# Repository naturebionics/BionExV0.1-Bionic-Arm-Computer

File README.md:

# BionExV0.1-Bionic-Arm-Computer
BionEx Bionic Limbs Computer

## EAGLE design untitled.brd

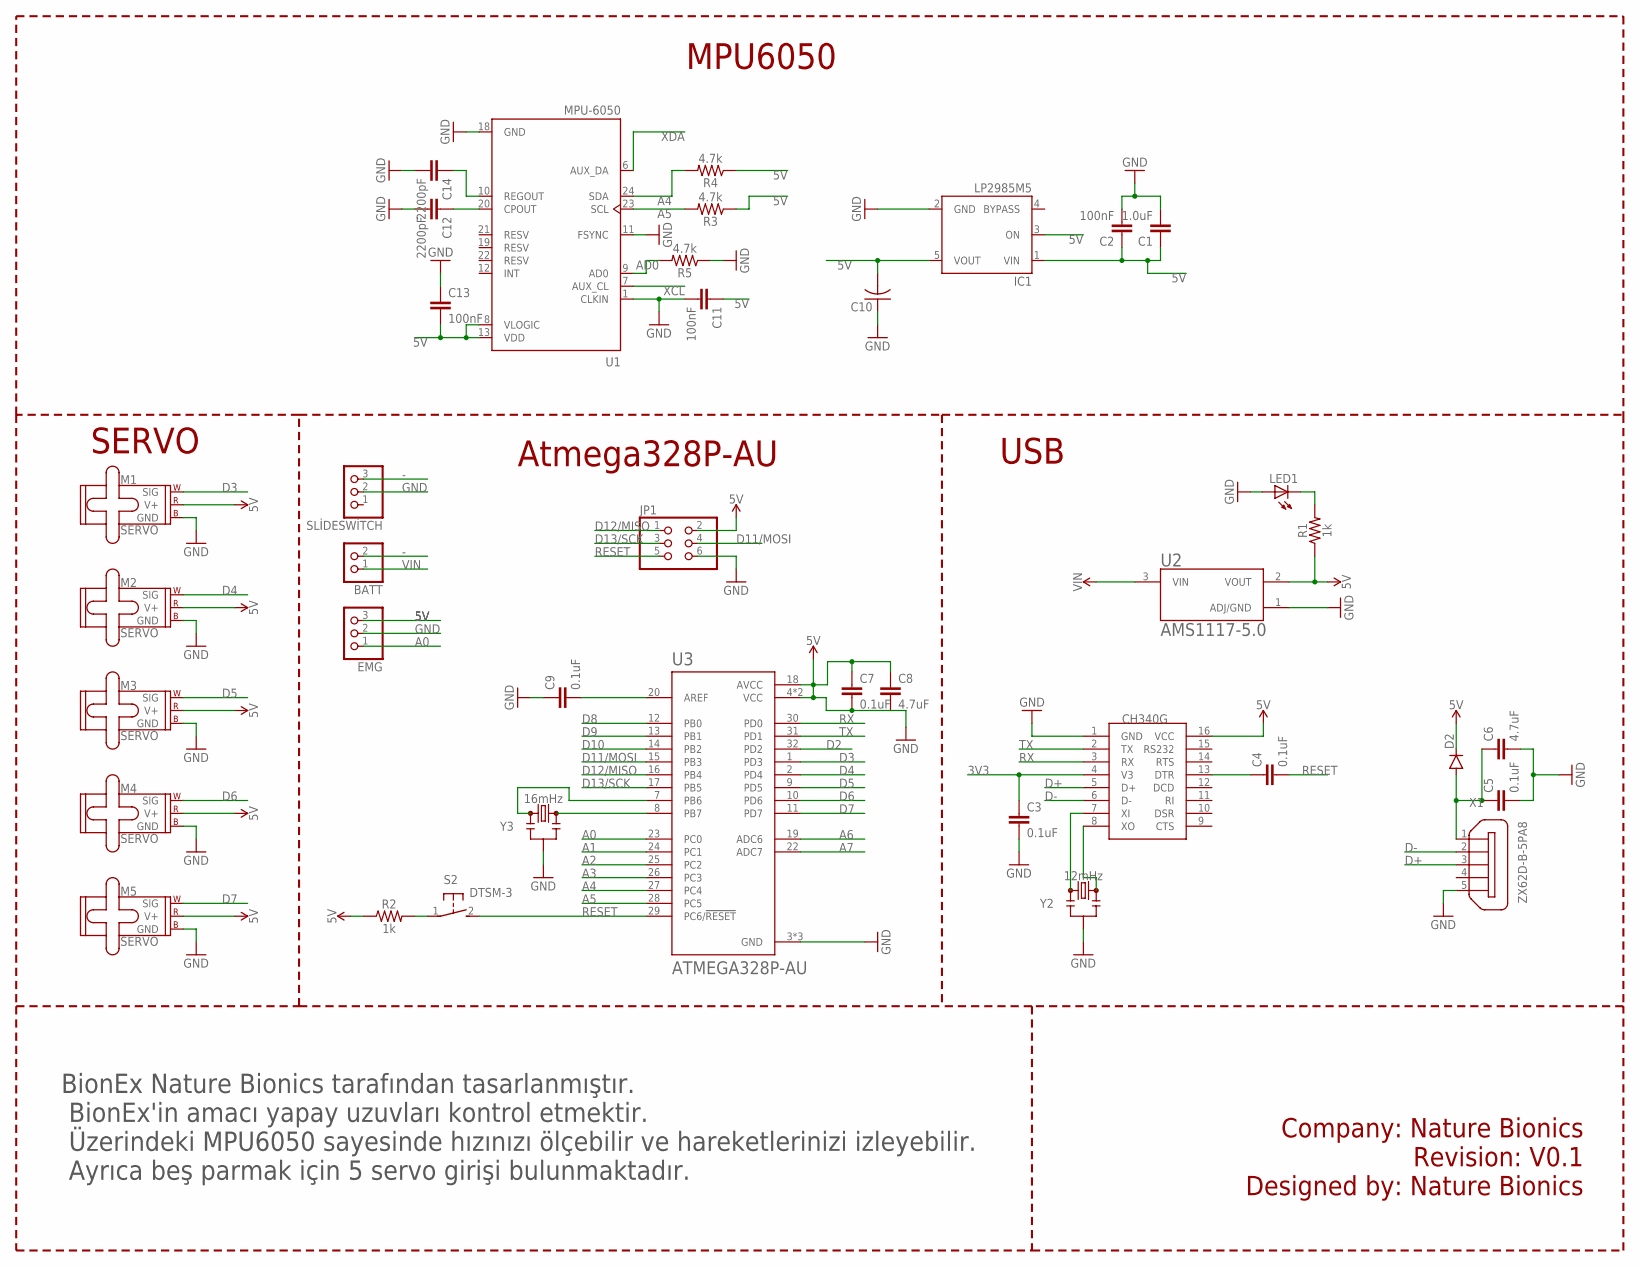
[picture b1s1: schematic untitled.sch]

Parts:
BATT: PINHD-1X2; 1X02
C1: 1.0uF; 0603
C2, C11, C13: 100nF; 0603
C3, C4, C5, C7, C9: 0.1uF; 0805
C6, C8: 4.7uF; 0603
C10: C-US_TANTALUM-1206(3216-METRIC); CAPM3216X180
C12, C14: 2200pF; 0603
D2: DIODE-SOD123; SOD123
EMG: PINHD-1X3; 1X03
IC1: LP2985M5; SOT23-5
JP1: PINHD-2X3; 2X03
LED1: LEDCHIP-LED0805; CHIP-LED0805
M1, M2, M3, M4, M5: SERVO; 1X03
R1, R2: 1k; 0603
R3, R4, R5: 4.7k; 0603
S2: DTSM-3
SLİDESWİTCH: PINHD-1X3; 1X03
U1: MPU-6050; QFN50P400X400X95-24N
U2: AMS1117-5.0; SOT229P700X180-4N
U3: ATMEGA328P-AU; QFP80P900X900X120-32N
U$1: CH340G; SOIC16
X1: ZX62D-B-5PA8
Y2: 12mHz; RESONATOR-SMD-3.2X1.3
Y3: 16mHz; RESONATOR-SMD-3.2X1.3

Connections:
3V3: C3.1, U$1.4 (V3)
5V: C1.1, C2.1, C10.2, C11.1, C13.2, D2.C, EMG.3, IC1.1 (VIN), IC1.3 (ON), IC1.5 (VOUT), JP1.2, M1.2 (V+), M2.2 (V+), M3.2 (V+), M4.2 (V+), M5.2 (V+), R1.1, R2.1, R3.1, R4.1, U1.8 (VLOGIC), U1.13 (VDD), U2.2 (VOUT), U$1.16 (VCC)
-: BATT.2, SLİDESWİTCH.3
A0: EMG.1, U3.23 (PC0)
A1: U3.24 (PC1)
A2: U3.25 (PC2)
A3: U3.26 (PC3)
A4: R4.2, U1.24 (SDA), U3.27 (PC4)
A5: R3.2, U1.23 (SCL), U3.28 (PC5)
A6: U3.19 (ADC6)
A7: U3.22 (ADC7)
AD0: R5.2, U1.9 (AD0)
D2: U3.32 (PD2)
D3: M1.1 (SIG), U3.1 (PD3)
D4: M2.1 (SIG), U3.2 (PD4)
D5: M3.1 (SIG), U3.9 (PD5)
D6: M4.1 (SIG), U3.10 (PD6)
D7: M5.1 (SIG), U3.11 (PD7)
D8: U3.12 (PB0)
D9: U3.13 (PB1)
D10: U3.14 (PB2)
D11/MOSI: JP1.4, U3.15 (PB3)
D12/MISO: JP1.1, U3.16 (PB4)
D13/SCK: JP1.3, U3.17 (PB5)
D+: U$1.5 (D+), X1.3
D-: U$1.6 (D-), X1.2
GND: C1.2, C2.2, C3.2, C5.2, C6.2, C7.1, C7.2, C8.1, C8.2, C9.1, C10.1, C11.2, C12.2, C13.1, C14.2, EMG.2, IC1.2 (GND), JP1.6, LED1.A, M1.3 (GND), M2.3 (GND), M3.3 (GND), M4.3 (GND), M5.3 (GND), R5.1, SLİDESWİTCH.2, U1.1 (CLKIN), U1.11 (FSYNC), U1.18 (GND), U2.1 (ADJ/GND), U3.3 (GND), U3.4 (VCC), U3.5 (GND), U3.6 (VCC), U3.18 (AVCC), U3.21 (GND), U$1.1 (GND), X1.5, Y2.2, Y3.2
unnamed: LED1.C, R1.2
unnamed: C12.1, U1.20 (CPOUT)
unnamed: C14.1, U1.10 (REGOUT)
unnamed: U$1.7 (XI), Y2.1
unnamed: U$1.8 (XO), Y2.3
unnamed: C4.1, U$1.13 (DTR)
unnamed: C5.1, C6.1, D2.A, X1.1
unnamed: R2.2, S2.1
unnamed: U3.8 (PB7), Y3.3
unnamed: U3.7 (PB6), Y3.1
unnamed: C9.2, U3.20 (AREF)
RESET: C4.2, JP1.5, S2.2, U3.29 (PC6/!RESET)
RX: U3.30 (PD0), U$1.3 (RX)
TX: U3.31 (PD1), U$1.2 (TX)
VIN: BATT.1, U2.3 (VIN)
XCL: U1.7 (AUX_CL)
XDA: U1.6 (AUX_DA)

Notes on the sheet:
Atmega328P-AU
USB
SERVO
MPU6050
BionEx Nature Bionics tarafından tasarlanmıştır. BionEx'in amacı yapay uzuvları kontrol etmektir. Üzerindeki MPU6050 sayesinde hızınızı ölçebilir ve hareketlerinizi izleyebilir. Ayrıca beş parmak için 5 servo girişi bulunmaktadır.
Company: Nature Bionics Revision: V0.1 Designed by: Nature Bionics

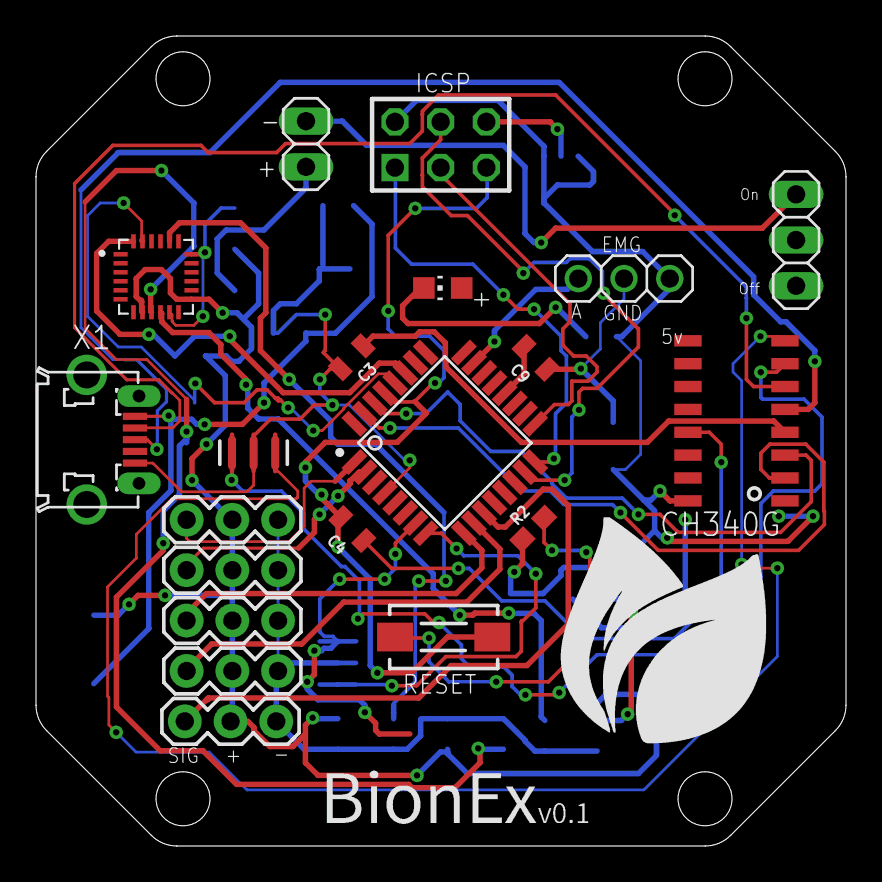
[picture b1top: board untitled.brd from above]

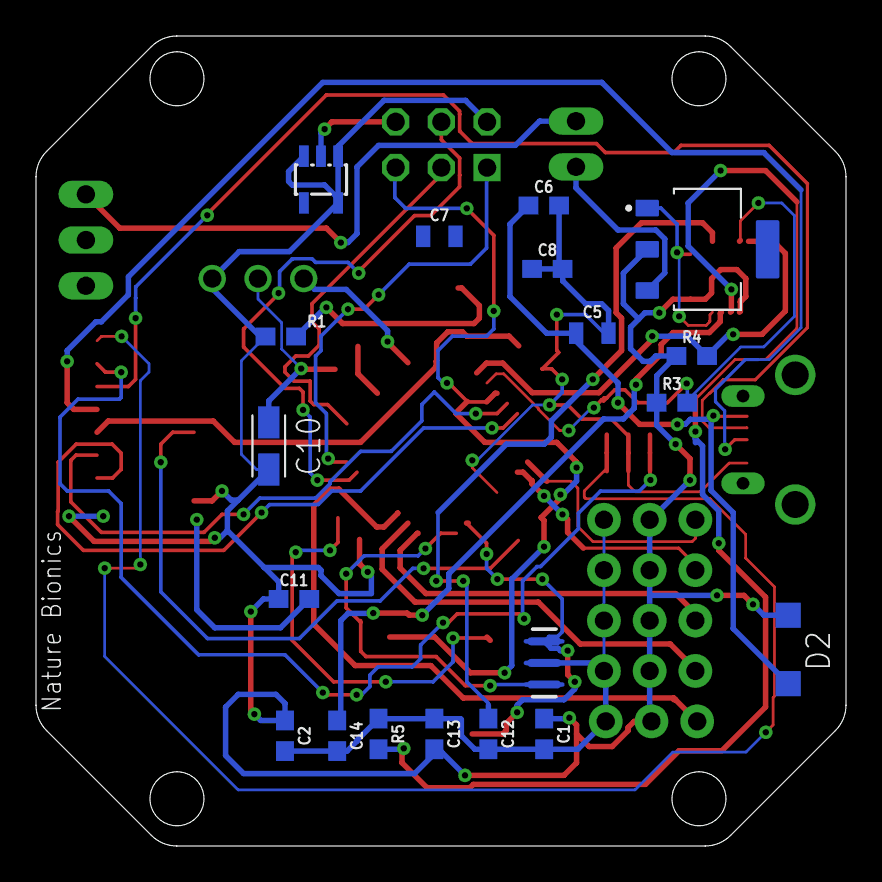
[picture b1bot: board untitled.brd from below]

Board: 2 copper layers, 45.0 x 45.0 mm, 39 parts (19 on the bottom side), 33 nets.

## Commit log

2021-05-08 BionEx Schematic & Board

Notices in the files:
parts and their libraries:
SparkFun-Capacitors: Licensing: Creative Commons ShareAlike 4.0 International - https://creativecommons.org/licenses/by-sa/4.0
